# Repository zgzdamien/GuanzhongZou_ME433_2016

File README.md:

Guanzhong Zou 04/01/2016
-------------------------

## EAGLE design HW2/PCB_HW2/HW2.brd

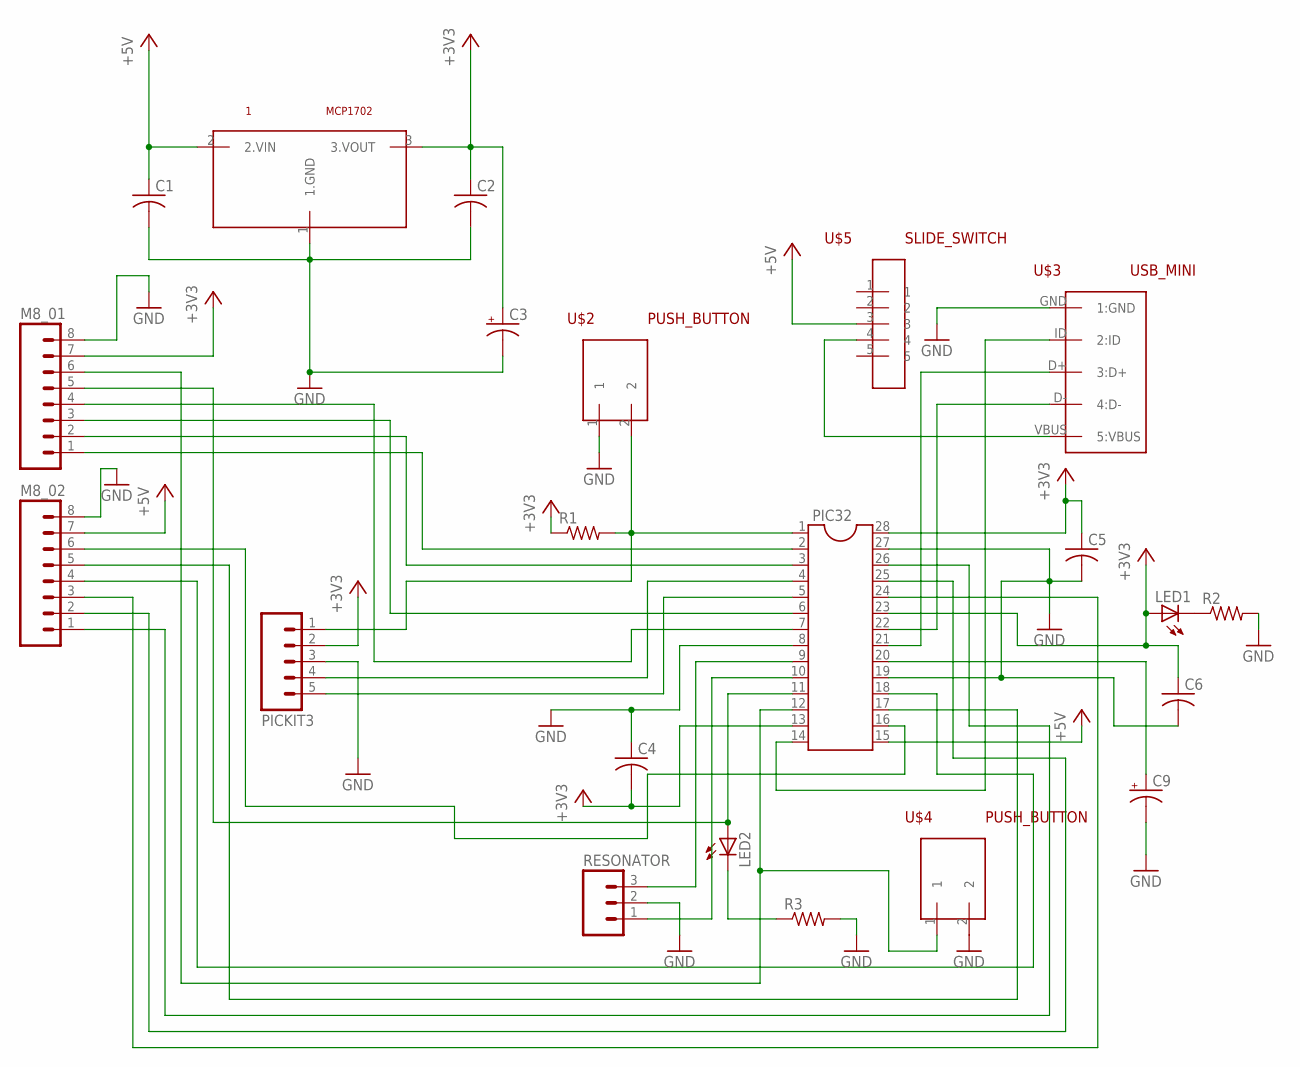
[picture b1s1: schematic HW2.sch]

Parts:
1: MCP1702; TO92
C1, C2, C4, C5, C6: C-US025-025X050; C025-025X050
C3, C9: CPOL-USE5-5; E5-5
LED1, LED2: LED3MM
M8_01, M8_02: M08; 1X08_ROUND
PIC32: DIL28-3
PICKIT3: M05PTH; 1X05
R1, R2, R3: R-US_0207/10; 0207/10
RESONATOR: M03PTH; 1X03
U$2, U$4: PUSH_BUTTON; 1X02_NO_SILK
U$3: USB_MINI; USB-MB-H
U$5: SLIDE_SWITCH; 1X05

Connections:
+3V3: 1.3 (3.VOUT), C2.1, C3.+, C4.2, C5.1, C6.1, LED1.A, M8_01.7, PIC32.13, PIC32.23, PIC32.28, PICKIT3.2, R1.1
+5V: 1.2 (2.VIN), C1.1, M8_02.7, PIC32.15, U$5.3
GND: 1.1 (1.GND), C1.2, C2.2, C3.-, C4.1, C5.2, C6.2, C9.-, M8_01.8, M8_02.8, PIC32.8, PIC32.19, PIC32.27, PICKIT3.3, R2.2, R3.2, RESONATOR.2, U$2.1, U$3.GND (1:GND), U$4.2
unnamed: PIC32.5, PICKIT3.5
unnamed: PIC32.1 (1:!MCLR), PICKIT3.1, R1.2, U$2.2
unnamed: U$3.VBUS (5:VBUS), U$5.4
unnamed: PIC32.14, U$3.ID (2:ID)
unnamed: PIC32.4, PICKIT3.4
unnamed: PIC32.21, U$3.D+ (3:D+)
unnamed: PIC32.22, U$3.D- (4:D-)
unnamed: PIC32.9, RESONATOR.3
unnamed: M8_01.1, PIC32.2 (2:A0)
unnamed: LED1.K (C), R2.1
unnamed: M8_01.2, PIC32.3
unnamed: PIC32.10, RESONATOR.1
unnamed: LED2.A, M8_01.5, PIC32.11
unnamed: LED2.K (C), R3.1
unnamed: M8_01.3, PIC32.6
unnamed: M8_01.6, PIC32.12, U$4.1
unnamed: M8_01.4, PIC32.7
unnamed: M8_02.2, PIC32.25
unnamed: M8_02.1, PIC32.26
unnamed: C9.+, PIC32.20
unnamed: M8_02.3, PIC32.24
unnamed: M8_02.4, PIC32.18
unnamed: M8_02.5, PIC32.17
unnamed: M8_02.6, PIC32.16

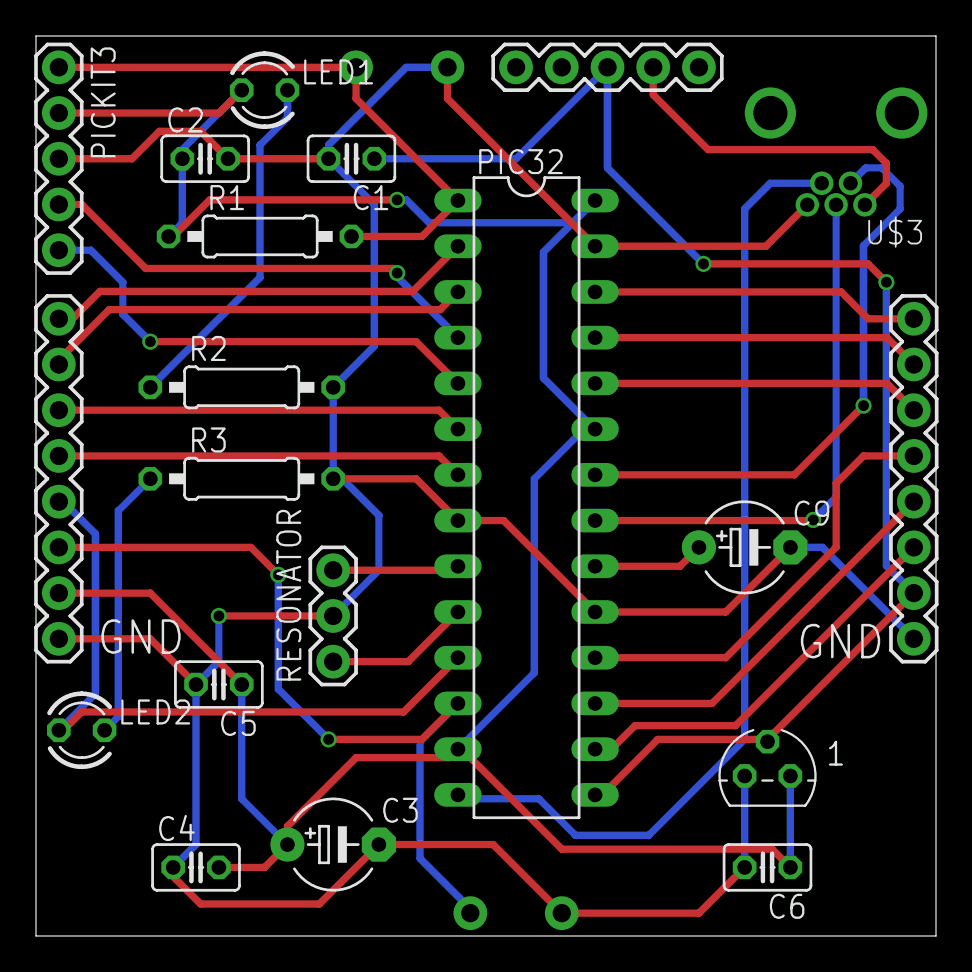
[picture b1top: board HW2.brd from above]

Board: 2 copper layers, 50.0 x 50.0 mm, 22 parts (0 on the bottom side), 27 nets.

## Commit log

2016-04-01 :neckbeard: Added .gitattributes & .gitignore files
2016-04-01 My First Commit!
2016-04-01 second line
2016-04-02 example_code
2016-04-02 example_code_C
2016-04-02 mplab_project
2016-04-02 initial
2016-04-02 Registers_configured
2016-04-04 HW1_code
2016-04-04 HW1_revised
2016-04-04 comment on code
2016-04-05 circuit diagram
2016-04-07 schematic_diagram_0
2016-04-08 HW2_Sch_finished
2016-04-10 PCB_Board
2016-04-13 Ready to be checked before order
2016-04-21 SPI-I2C
2016-04-28 HW4_Update1
2016-04-29 HW4_I2C_Final
2016-04-29 HW6_initial
2016-05-22 Add to HW6 RPA1,RPB15
2016-05-24 HW5 Draw string on LCD finished
2016-05-24 HW5_FINISHED
2016-06-09 HW4_finished
2016-06-09 LaserCutting_finished
2016-06-10 last_update
